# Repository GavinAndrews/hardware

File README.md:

# Nivag Swerdna's Shared Hardware Projects
This repository contains designs that have been publically shared and may be reproduced under GPL v2. i.e. That any derived versions should include full schematics and acknowledgement of the original work, and themselves be subject to the same licencing.

_"Share & Enjoy"_ 
## ROMulan PET RAMulator (with EAzy NOPulation) Version 4.1

A ROM and RAM replacement board for 6502 based microprocessors, particularly Commodore PETs and their variants.
Features include:
* 32MB RAM replacement $0000-$7FFF
* ROM replacement $9000-$FFFF selectable
* 16 individual ROM Sets stored in 4Mb Flash
* NOP Generation (causes $EA NOP to be presented to CPU on all reads)
* Power LED
* Onboard Reset switch
 
 For historic reasons this board is refered to as memory and found in the memory\ subdirectory
     
## OMNI ROMulator

A 6540 ROM replacement board for 6502 based microprocessors, particularly original Commodore PETs and their variants.
Features include:
* 32MB ROM containing 16 x 2KB Pages
* Either 2KB or 4KB ROM Replacement
* Machined Edge pins for a original chip look and feel
* Selections made using resolderable jumpers
 
 For historic reasons this board is refered to as 6540replacement and found in the 6540replacement\ subdirectory

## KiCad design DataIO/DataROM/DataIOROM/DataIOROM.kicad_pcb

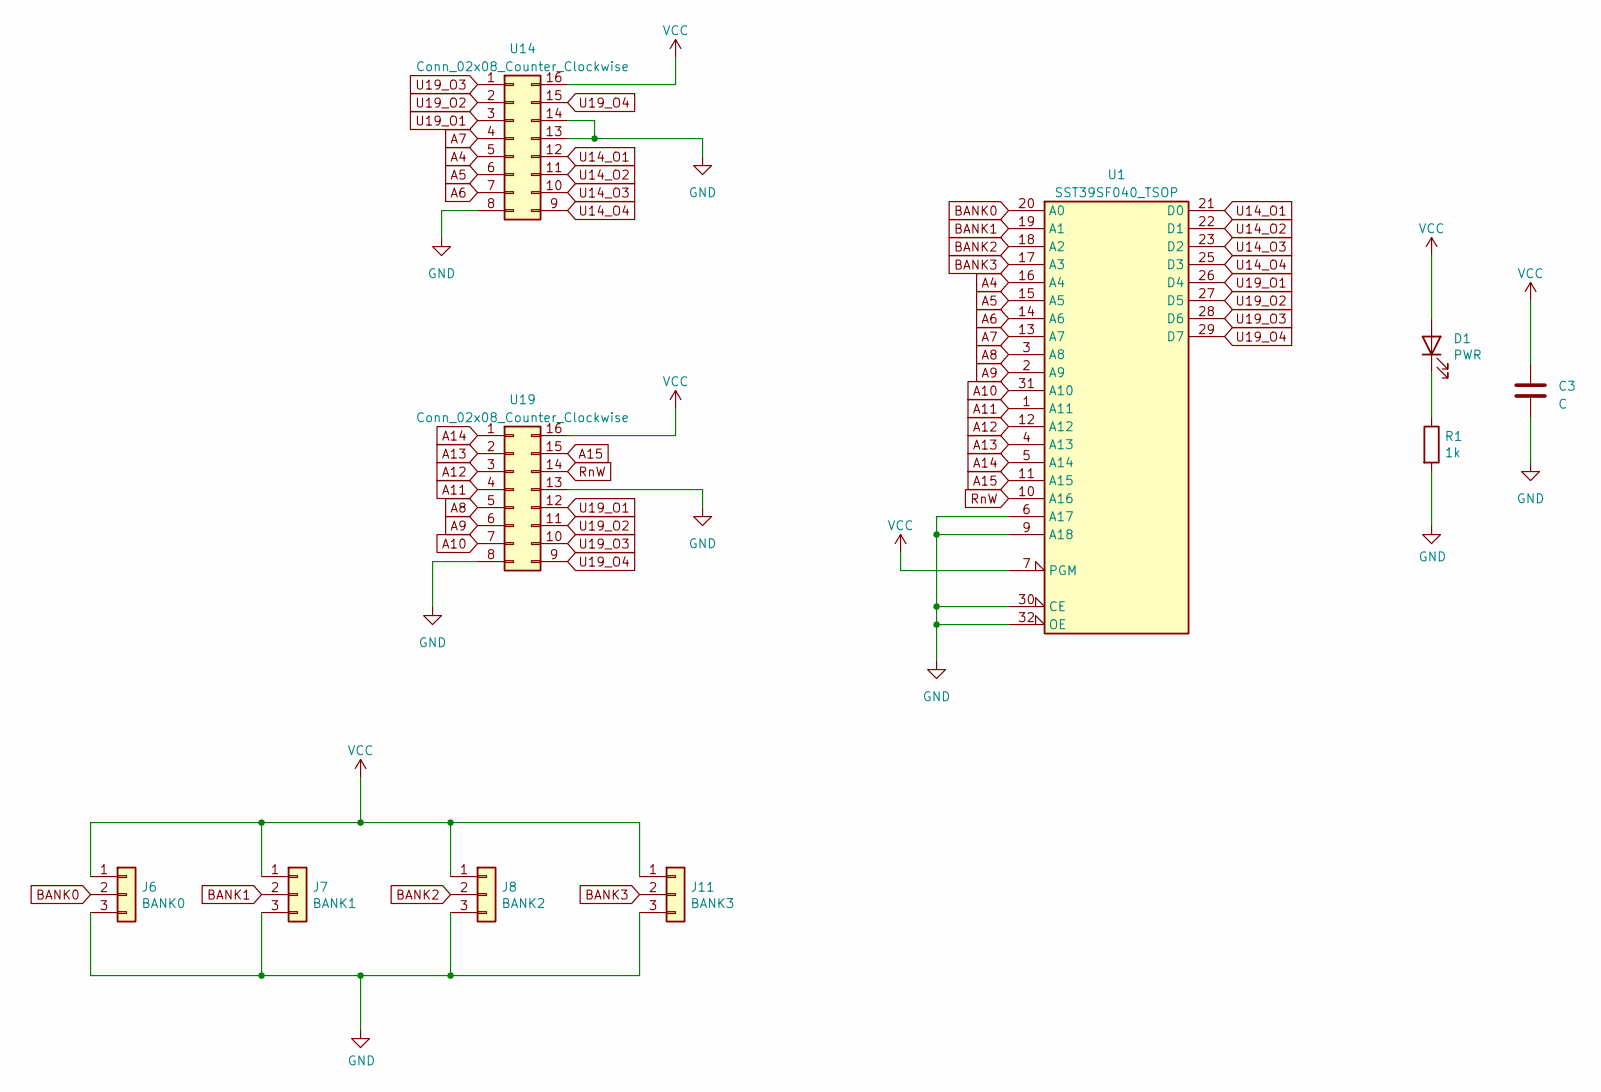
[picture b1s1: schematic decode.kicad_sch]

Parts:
C3: C; C_0603_1608Metric
D1: PWR; LED_0603_1608Metric
J6: BANK0; JP2_Arrow
J7: BANK1; JP2_Arrow
J8: BANK2; JP2_Arrow
J11: BANK3; JP2_Arrow
R1: 1k; R_0603_1608Metric
U1: SST39SF040_TSOP; TSOP-I-32_14mmx8mm_P0.5mm
U14, U19: Conn_02x08_Counter_Clockwise; DIP-16_W7.62mm

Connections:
A4: U1.16 (A4), U14.5; also elsewhere on the board
A5: U1.15 (A5), U14.6; also elsewhere on the board
A6: U1.14 (A6), U14.7; also elsewhere on the board
A7: U1.13 (A7), U14.4; also elsewhere on the board
A8: U1.3 (A8), U19.5; also elsewhere on the board
A9: U1.2 (A9), U19.6; also elsewhere on the board
A10: U1.31 (A10), U19.7; also elsewhere on the board
A11: U1.1 (A11), U19.4; also elsewhere on the board
A12: U1.12 (A12), U19.3; also elsewhere on the board
A13: U1.4 (A13), U19.2; also elsewhere on the board
A14: U1.5 (A14), U19.1
A15: U1.11 (A15), U19.15
BANK0: J6.2, U1.20 (A0)
BANK1: J7.2, U1.19 (A1)
BANK2: J8.2, U1.18 (A2)
BANK3: J11.2, U1.17 (A3)
GND: C3.2, J6.3, J7.3, J8.3, J11.3, R1.2, U1.6 (A17), U1.9 (A18), U1.24 (GND), U1.30 (CE), U1.32 (OE), U14.8, U14.13, U14.14, U19.8, U19.13; also elsewhere on the board
unnamed: D1.1 (K), R1.1
RnW: U1.10 (A16), U19.14
U14_O1: U1.21 (D0), U14.12
U14_O2: U1.22 (D1), U14.11
U14_O3: U1.23 (D2), U14.10
U14_O4: U1.25 (D3), U14.9
U19_O1: U1.26 (D4), U14.3, U19.12
U19_O2: U1.27 (D5), U14.2, U19.11
U19_O3: U1.28 (D6), U14.1, U19.10
U19_O4: U1.29 (D7), U14.15, U19.9
VCC: C3.1, D1.2 (A), J6.1, J7.1, J8.1, J11.1, U1.7 (PGM), U1.8 (VCC), U14.16, U19.16; also elsewhere on the board

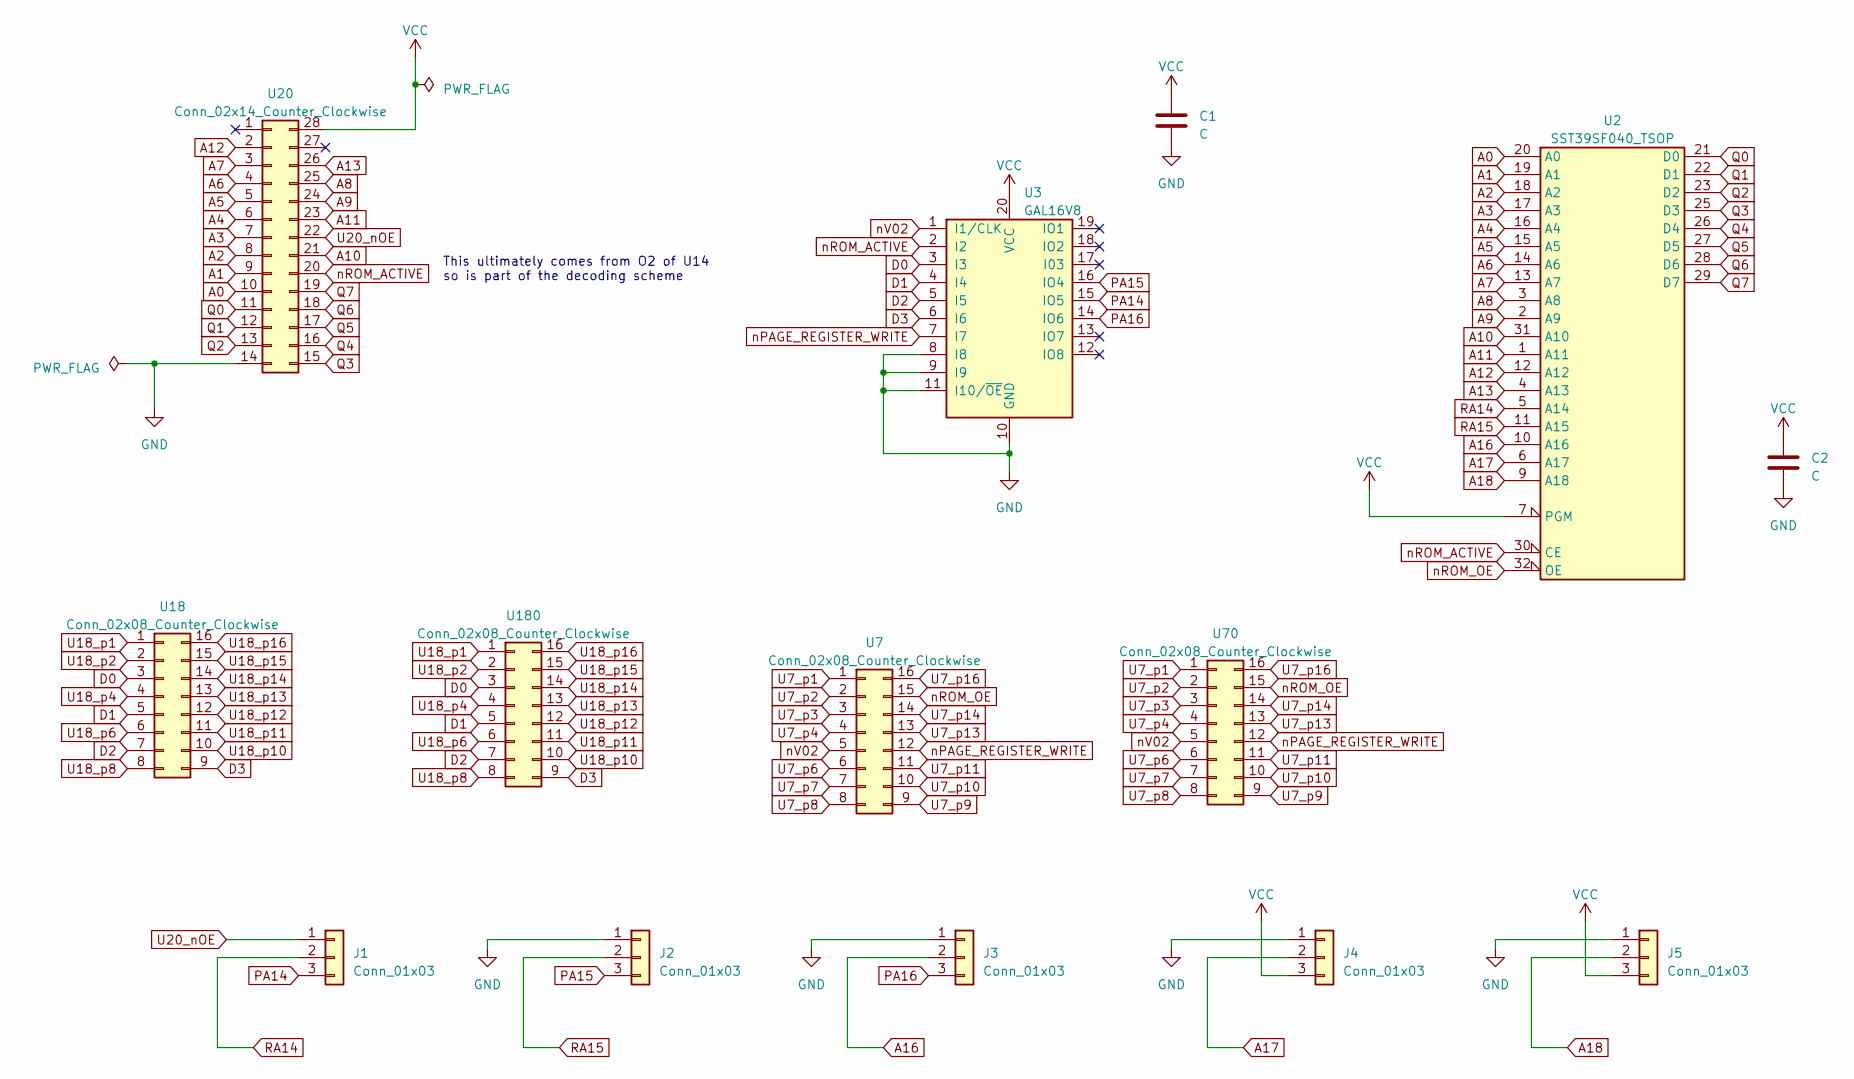
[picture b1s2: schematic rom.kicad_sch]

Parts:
C1, C2: C; C_0603_1608Metric
J1, J2, J3, J4, J5: Conn_01x03; JP2_Arrow
U2: SST39SF040_TSOP; TSOP-I-32_14mmx8mm_P0.5mm
U3: GAL16V8; DIP-20_W7.62mm_Socket
U7, U18: Conn_02x08_Counter_Clockwise; DIP-16_Frame_Bottom
U20: Conn_02x14_Counter_Clockwise; DIP-28_W15.24mm
U70, U180: Conn_02x08_Counter_Clockwise; DIP-16_Frame

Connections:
A0: U2.20 (A0), U20.10
A1: U2.19 (A1), U20.9
A2: U2.18 (A2), U20.8
A3: U2.17 (A3), U20.7
A4: U2.16 (A4), U20.6; also elsewhere on the board
A5: U2.15 (A5), U20.5; also elsewhere on the board
A6: U2.14 (A6), U20.4; also elsewhere on the board
A7: U2.13 (A7), U20.3; also elsewhere on the board
A8: U2.3 (A8), U20.25; also elsewhere on the board
A9: U2.2 (A9), U20.24; also elsewhere on the board
A10: U2.31 (A10), U20.21; also elsewhere on the board
A11: U2.1 (A11), U20.23; also elsewhere on the board
A12: U2.12 (A12), U20.2; also elsewhere on the board
A13: U2.4 (A13), U20.26; also elsewhere on the board
A16: J3.2, U2.10 (A16)
A17: J4.2, U2.6 (A17)
A18: J5.2, U2.9 (A18)
D0: U3.3 (I3), U18.3, U180.3
D1: U3.4 (I4), U18.5, U180.5
D2: U3.5 (I5), U18.7, U180.7
D3: U3.6 (I6), U18.9, U180.9
GND: C1.2, C2.2, J2.1, J3.1, J4.1, J5.1, U2.24 (GND), U3.8 (I8), U3.9 (I9), U3.10 (GND), U3.11 (I10/~OE), U20.14; also elsewhere on the board
PA14: J1.3, U3.15 (IO5)
PA15: J2.3, U3.16 (IO4)
PA16: J3.3, U3.14 (IO6)
Q0: U2.21 (D0), U20.11
Q1: U2.22 (D1), U20.12
Q2: U2.23 (D2), U20.13
Q3: U2.25 (D3), U20.15
Q4: U2.26 (D4), U20.16
Q5: U2.27 (D5), U20.17
Q6: U2.28 (D6), U20.18
Q7: U2.29 (D7), U20.19
RA14: J1.2, U2.5 (A14)
RA15: J2.2, U2.11 (A15)
U7_p1: U7.1, U70.1
U7_p2: U7.2, U70.2
U7_p3: U7.3, U70.3
U7_p4: U7.4, U70.4
U7_p6: U7.6, U70.6
U7_p7: U7.7, U70.7
U7_p8: U7.8, U70.8
U7_p9: U7.9, U70.9
U7_p10: U7.10, U70.10
U7_p11: U7.11, U70.11
U7_p13: U7.13, U70.13
U7_p14: U7.14, U70.14
U7_p16: U7.16, U70.16
U18_p1: U18.1, U180.1
U18_p2: U18.2, U180.2
U18_p4: U18.4, U180.4
U18_p6: U18.6, U180.6
U18_p8: U18.8, U180.8
U18_p10: U18.10, U180.10
U18_p11: U18.11, U180.11
U18_p12: U18.12, U180.12
U18_p13: U18.13, U180.13
U18_p14: U18.14, U180.14
U18_p15: U18.15, U180.15
U18_p16: U18.16, U180.16
U20_nOE: J1.1, U20.22
VCC: C1.1, C2.1, J4.3, J5.3, U2.7 (PGM), U2.8 (VCC), U3.20 (VCC), U20.28; also elsewhere on the board
nPAGE_REGISTER_WRITE: U3.7 (I7), U7.12, U70.12
nROM_ACTIVE: U2.30 (CE), U3.2 (I2), U20.20
nROM_OE: U2.32 (OE), U7.15, U70.15
nV02: U3.1 (I1/CLK), U7.5, U70.5

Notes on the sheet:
This ultimately comes from O2 of U14 so is part of the decoding scheme

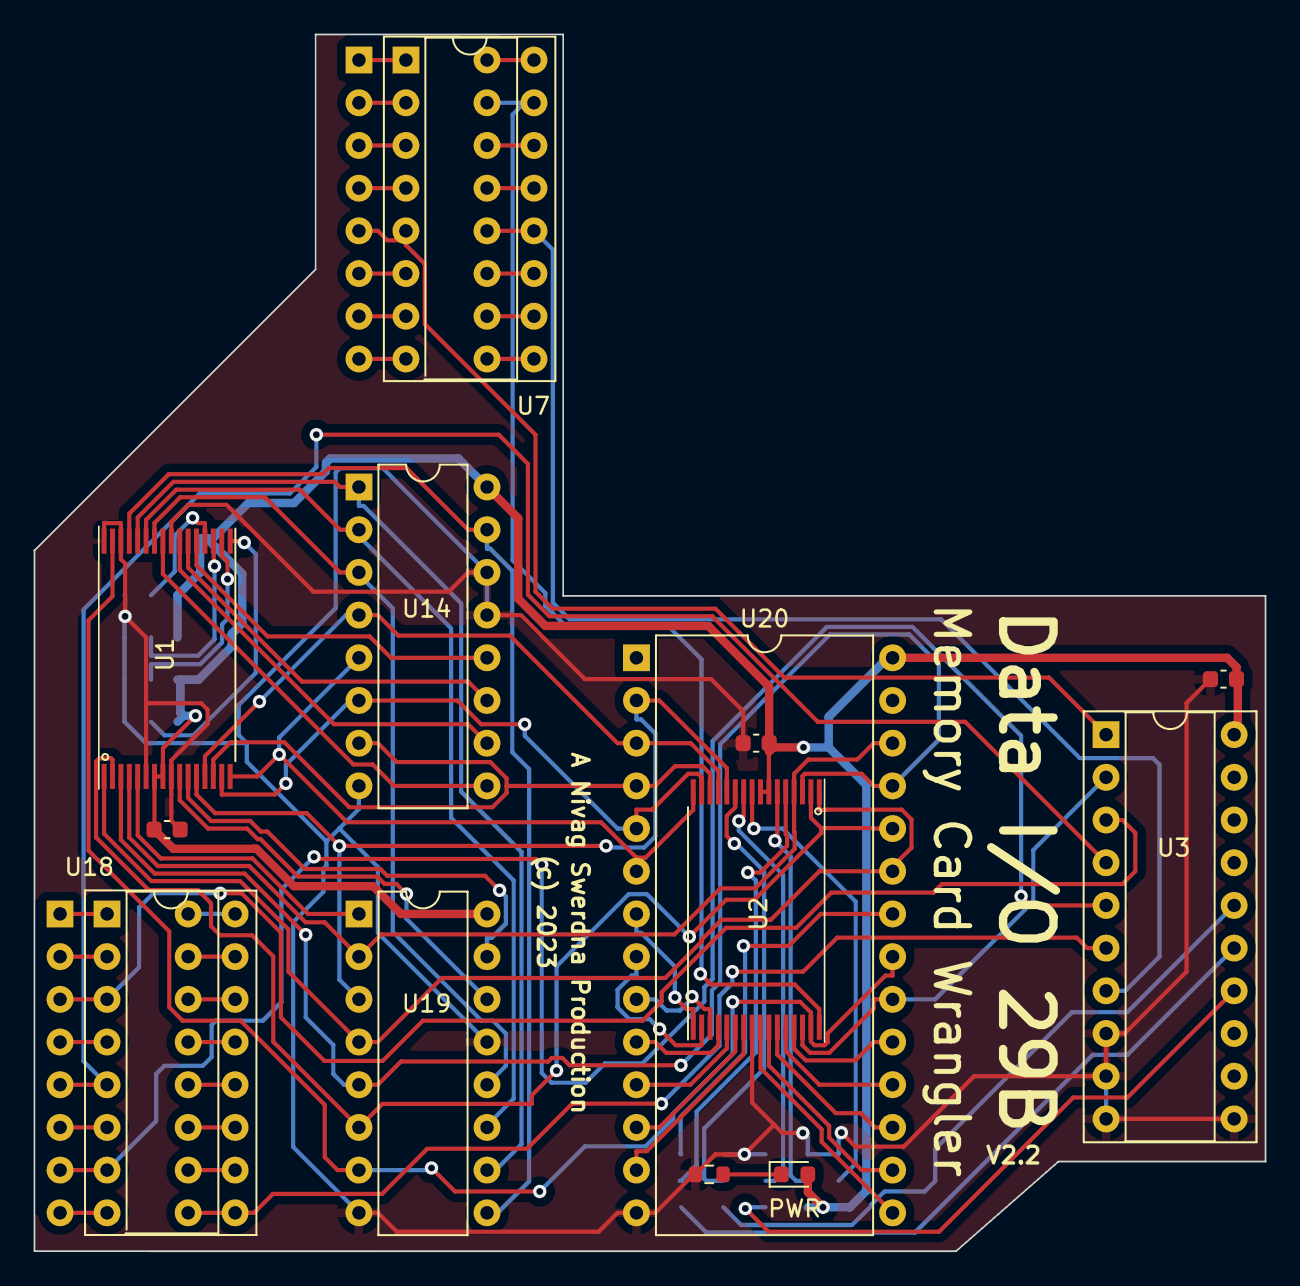
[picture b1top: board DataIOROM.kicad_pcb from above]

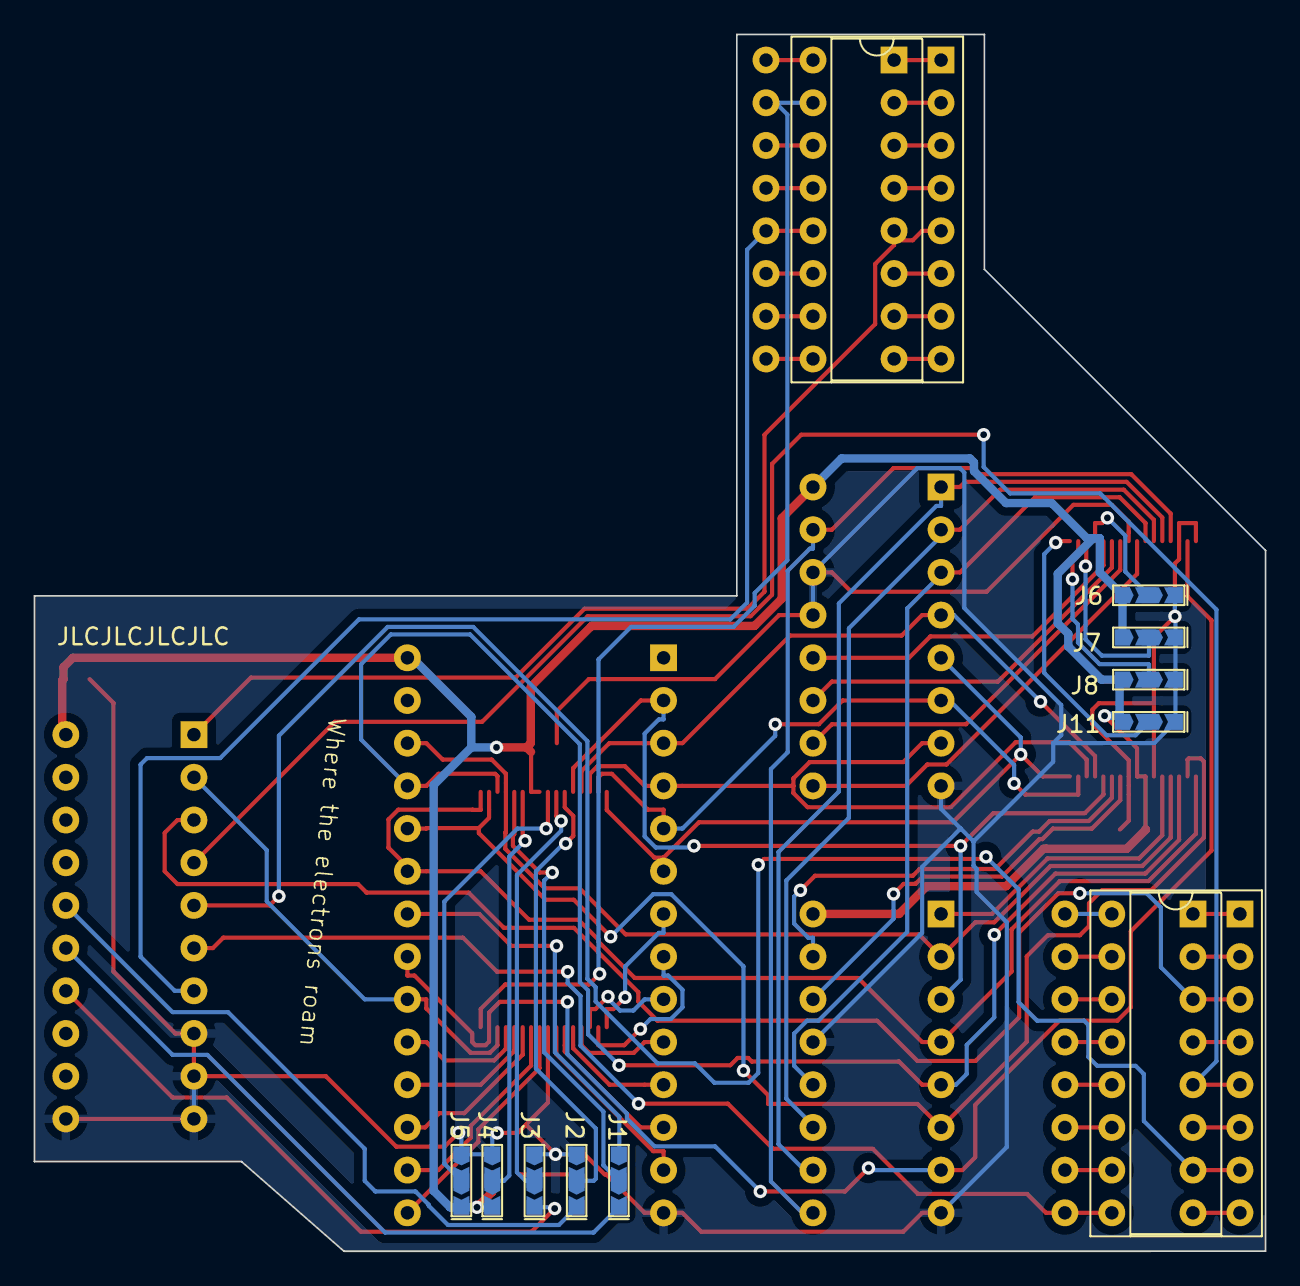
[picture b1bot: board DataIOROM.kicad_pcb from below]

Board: 2 copper layers, 73.2 x 72.4 mm, 24 parts (9 on the bottom side), 82 nets.

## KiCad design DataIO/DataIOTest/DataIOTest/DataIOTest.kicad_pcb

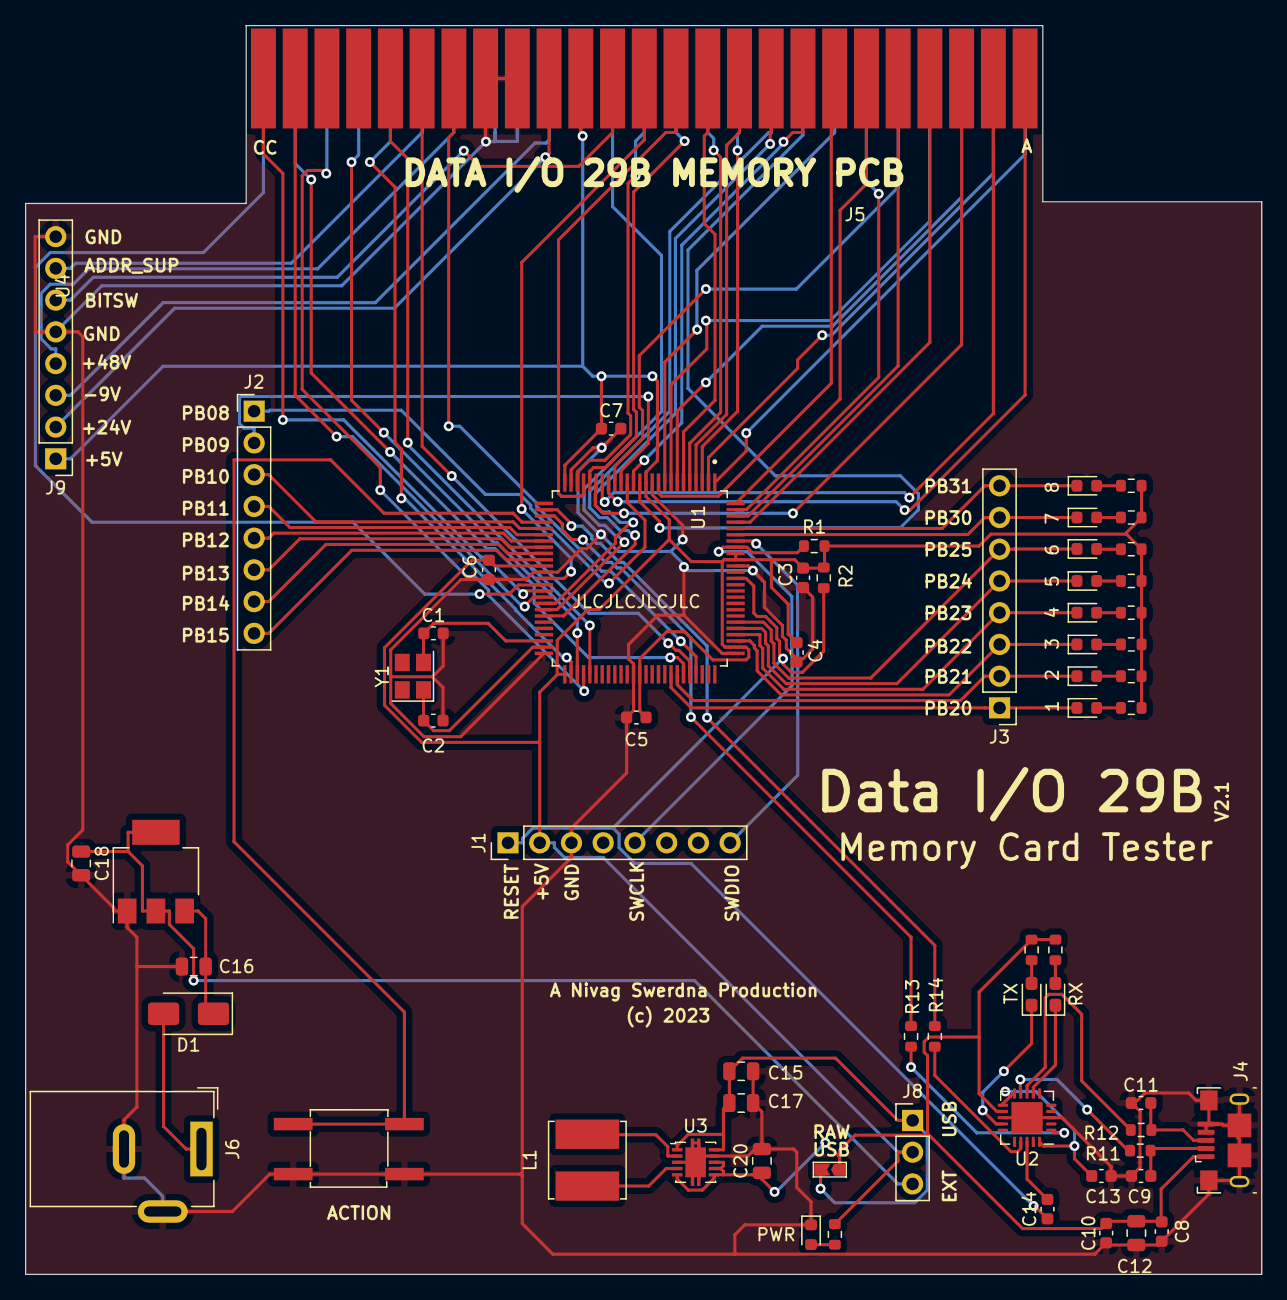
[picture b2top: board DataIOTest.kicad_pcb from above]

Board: 2 copper layers, 98.9 x 99.9 mm, 64 parts (0 on the bottom side), 96 nets.

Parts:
C1, C2: 8p; C_0603_1608Metric
C3, C4, C5, C7: .1u; C_0603_1608Metric
C6: 1u; C_0603_1608Metric
C8: 10n; C_0603_1608Metric
C9, C11: 47p; C_0603_1608Metric
C10, C13, C14: 100n; C_0603_1608Metric
C12: 10u; C_0805_2012Metric
C15, C17, C18, C20: 22u; C_0805_2012Metric
C16: 10u 16V; C_0805_2012Metric
D1: M7; D_SMA
J1, J2, J3, J9: Conn_01x08; PinHeader_1x08_P2.54mm_Vertical
J4: USB_B_Micro; USB_Micro-B_10118193
J5: MEMORY CARD; DATAIO_MEMORY_CONNECTOR
J6: Barrel_Jack_Switch; DC10A
J7: USB_RAW; JP1_Arrow
J8: PWR_SELECT; PinHeader_1x03_P2.54mm_Vertical
L1: 4.7u; L_Bourns_SRN6045TA
LED1: 1; LED_0603_1608Metric
LED2: 2; LED_0603_1608Metric
LED3: 3; LED_0603_1608Metric
LED4: 4; LED_0603_1608Metric
LED5: 5; LED_0603_1608Metric
LED6: 6; LED_0603_1608Metric
LED7: 7; LED_0603_1608Metric
LED8: 8; LED_0603_1608Metric
LED9: TX; LED_0603_1608Metric_Pad1.05x0.95mm_HandSolder
LED10: RX; LED_0603_1608Metric_Pad1.05x0.95mm_HandSolder
LED11: PWR; LED_0603_1608Metric
R1, R2, R3, R4, R5, R6, R7, R8, R9, R10: 10k; R_0603_1608Metric
R11, R12: 27; R_0603_1608Metric
R13, R14, R15, R16, R17: 1k; R_0603_1608Metric
SW1: Tactile_Switch; TACTILE_SW
U1: ATSAMC21N18A-ANT; QFP50P1600X1600X120-100N
U2: FT231XQ; QFN-20-1EP_4x4mm_P0.5mm_EP2.5x2.5mm
U3: TPS63002DRCT; VSON-10-1EP_3x3mm_P0.5mm_EP1.65x2.4mm
U4: AP1117-50; SOT-223-3_TabPin2
Y1: 16MHz; Crystal_SMD_3225-4Pin_3.2x2.5mm

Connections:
+5V: C3.1, C4.1, C5.1, C6.1, C7.1, J1.2, J5.15 (+5V), J5.S (+5V), J8.2, J9.1, R1.1, R2.1, R3.2, R4.2, R5.2, R6.2, R7.2, R8.2, R9.2, R10.2, R17.2, U1.12 (VDDANA), U1.25 (VDDIO), U1.36 (VDDIO), U1.51 (VDDIO), U1.63 (VDDIO), U1.77 (VDDIO), U1.91 (VDDCORE), U1.92 (VDDIN)
+24V: J5.T (+24V), J9.2
+48V: J5.19 (+48V), J9.4
-9V: J5.16 (-9V), J9.3
A0: J5.1 (A0), U1.1 (PA00)
A1: J5.2 (A1), U1.2 (PA01)
A2: J5.3 (A2), U1.7 (PA02)
A3: J5.4 (A3), U1.8 (PA03)
A4: J5.5 (A4), U1.17 (PA04)
A5: J5.A (A5), U1.18 (PA05)
A6: J5.B (A6), U1.19 (PA06)
A7: J5.C (A7), U1.20 (PA07)
A8: J5.D (A8), U1.97 (PB00)
A9: J5.E (A9), U1.98 (PB01)
A10: J5.6 (A10), U1.99 (PB02)
A11: J5.F (A11), U1.100 (PB03)
A12: J5.7 (A12), U1.9 (PB04)
A13: J5.H (A13), U1.10 (PB05)
A14: J5.8 (A14), U1.13 (PB06)
A15: J5.J (A15), U1.14 (PB07)
ADDR_SUP: J5.20 (ADDR_SUP), J9.7
BITSW: J5.R (BITSW), J9.6
C1: J5.21 (C1), U1.52 (PA16)
C2: J5.22 (C2), U1.53 (PA17)
DO1: J5.10 (DO1), U1.3 (PC00)
DO2: J5.L (DO2), U1.4 (PC01)
DO3: J5.11 (DO3), U1.5 (PC02)
DO4: J5.M (DO4), U1.6 (PC03)
DO5: J5.12 (DO5), U1.21 (PC05)
DO6: J5.N (DO6), U1.22 (PC06)
DO7: J5.13 (DO7), U1.23 (PC07)
DO8: J5.P (DO8), U1.38 (PC08)
EXT_5V: C18.1, J8.3, U4.2 (VO)
GATE_ENABLE: J5.W (GATE_ENABLE), U1.72 (PA22)
GND: C1.2, C2.2, C3.2, C4.2, C5.2, C6.2, C7.2, C8.1, C9.1, C10.1, C11.1, C12.1, C13.1, C15.2, C16.2, C17.2, C18.2, C20.2, J1.3, J4.4 (ID), J4.5 (GND), J4.6 (Shield), J5.17 (GND), J5.18 (GND), J5.U (GND), J5.V (GND), J6.2, J6.3, J9.5, J9.8, LED11.1 (K), SW1.3, SW1.4, U1.11 (GND), U1.24 (GND), U1.37 (GND), U1.50 (GND), U1.62 (GND), U1.76 (GND), U1.90 (GND), U2.3 (GND), U2.13 (GND), U2.21 (GND), U3.3 (PGND), U3.9 (GND), U3.11 (PAD), U4.1 (GND)
LED1: J3.1, LED1.1 (K), U1.68 (PB20)
LED2: J3.2, LED2.1 (K), U1.69 (PB21)
LED3: J3.3, LED3.1 (K), U1.78 (PB22)
LED4: J3.4, LED4.1 (K), U1.79 (PB23)
LED5: J3.5, LED5.1 (K), U1.80 (PB24)
LED6: J3.6, LED6.1 (K), U1.81 (PB25)
LED7: J3.7, LED7.1 (K), U1.95 (PB30)
LED8: J3.8, LED8.1 (K), U1.96 (PB31)
MCU_RESET: C14.1, J1.1, R2.2, U1.88 (~RESET)
unnamed: D1.2 (A), J6.1
unnamed: C16.1, D1.1 (K), U4.3 (VI)
unnamed: J2.1, U1.15 (PB08)
unnamed: J2.2, U1.16 (PB09)
unnamed: J2.3, U1.30 (PB10)
unnamed: J2.4, U1.31 (PB11)
unnamed: J2.5, U1.32 (PB12)
unnamed: J2.6, U1.33 (PB13)
unnamed: J2.7, U1.34 (PB14)
unnamed: J2.8, U1.35 (PB15)
unnamed: C11.2, J4.3 (D+), R12.2
unnamed: C9.2, J4.2 (D-), R11.2
unnamed: LED1.2 (A), R3.1
unnamed: LED2.2 (A), R5.1
unnamed: LED3.2 (A), R7.1
unnamed: LED4.2 (A), R9.1
unnamed: LED5.2 (A), R4.1
unnamed: LED6.2 (A), R6.1
unnamed: LED7.2 (A), R8.1
unnamed: LED8.2 (A), R10.1
unnamed: LED9.2 (A), R15.1
unnamed: LED9.1 (K), U2.14 (CBUS1)
unnamed: LED10.2 (A), R16.1
unnamed: LED10.1 (K), U2.7 (CBUS2)
unnamed: LED11.2 (A), R17.1
unnamed: C13.2, U2.10 (3V3OUT), U2.11 (~RESET), U2.20 (VCCIO)
unnamed: R14.2, U2.1 (RXD)
unnamed: R13.1, U2.17 (TXD)
unnamed: R11.1, U2.9 (USBDM)
unnamed: R12.1, U2.8 (USBDP)
unnamed: C14.2, U2.18 (~DTR)
unnamed: L1.1, U3.4 (L1)
unnamed: L1.2, U3.2 (L2)
OVER_C: J5.K (OVER_C), U1.42 (PC12)
P1nP0: J5.BB (P1nP0), U1.41 (PC11)
RX: R13.2, U1.27 (PA09)
RnW: J5.CC (RnW), U1.40 (PC10)
SW1: SW1.1, SW1.2, U1.29 (PA11)
SWCLK: J1.5, R1.2, U1.93 (PA30)
SWDIO: J1.8, U1.94 (PA31)
TX: R14.1, U1.28 (PA10)
USB_5V: C15.1, C17.1, J7.2, J8.1, U3.1 (VOUT), U3.10 (FB)
USB_PWR: C8.2, C10.2, C12.2, C20.1, J4.1 (VBUS), J7.1, R15.2, R16.2, U2.12 (VCC), U3.5 (VIN), U3.6 (EN), U3.7 (PS_SYNC), U3.8 (VINA)
XIN: C1.1, U1.48 (PA14), Y1.2
XOUT: C2.1, U1.49 (PA15), Y1.1
nC3: J5.23 (nC3), U1.54 (PA18)
nC4: J5.Y (nC4), U1.55 (PA19)
nC7: J5.24 (nC7), U1.70 (PA20)
nC11: J5.X (nC11), U1.71 (PA21)
nPULSE: J5.9 (nPULSE), U1.44 (PC14)
nV02: J5.25 (nV02), U1.39 (PC09)
nVPULSE: J5.14 (nVPULSE), U1.43 (PC13)

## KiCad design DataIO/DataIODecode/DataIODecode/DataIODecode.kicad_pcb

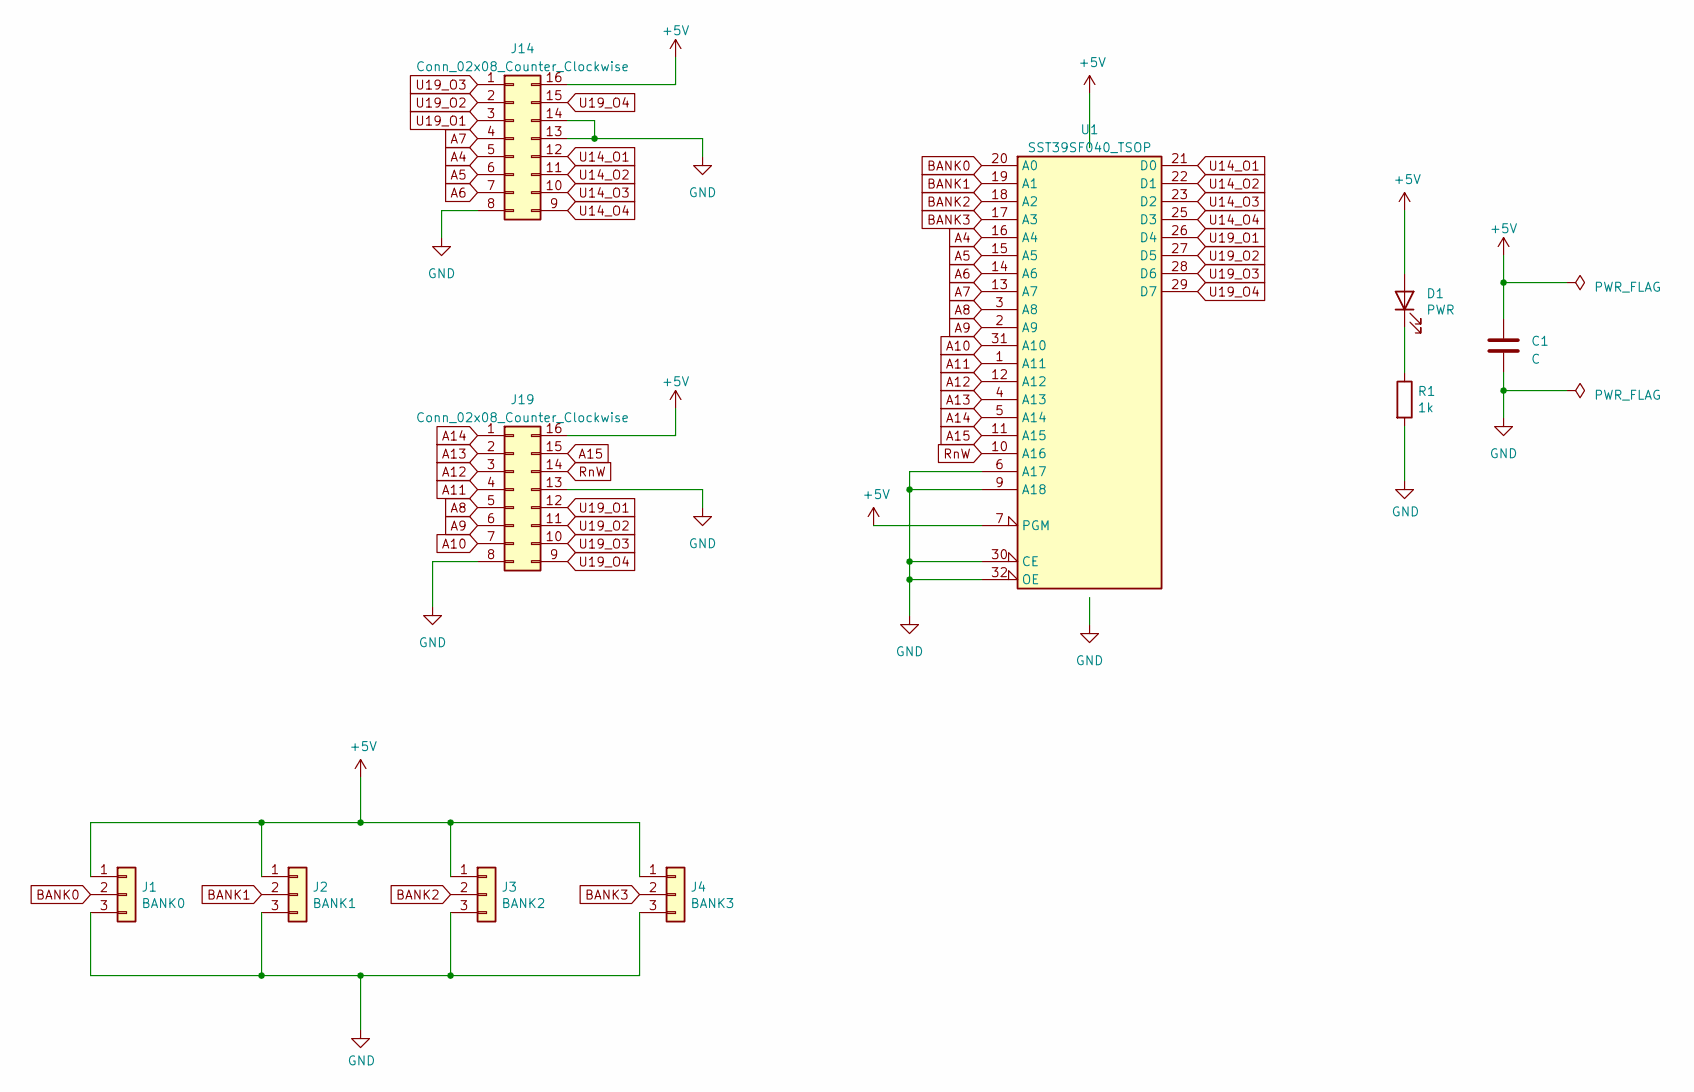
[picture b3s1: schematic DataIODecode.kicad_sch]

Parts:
C1: C; C_0603_1608Metric
D1: PWR; LED_0603_1608Metric
J1: BANK0; JP2_Arrow
J2: BANK1; JP2_Arrow
J3: BANK2; JP2_Arrow
J4: BANK3; JP2_Arrow
J14, J19: Conn_02x08_Counter_Clockwise; DIP-16_W7.62mm
R1: 1k; R_0603_1608Metric
U1: SST39SF040_TSOP; TSOP-I-32_14mmx8mm_P0.5mm

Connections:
+5V: C1.1, D1.2 (A), J1.1, J2.1, J3.1, J4.1, J14.16, J19.16, U1.7 (PGM), U1.8 (VCC)
A4: J14.5, U1.16 (A4)
A5: J14.6, U1.15 (A5)
A6: J14.7, U1.14 (A6)
A7: J14.4, U1.13 (A7)
A8: J19.5, U1.3 (A8)
A9: J19.6, U1.2 (A9)
A10: J19.7, U1.31 (A10)
A11: J19.4, U1.1 (A11)
A12: J19.3, U1.12 (A12)
A13: J19.2, U1.4 (A13)
A14: J19.1, U1.5 (A14)
A15: J19.15, U1.11 (A15)
BANK0: J1.2, U1.20 (A0)
BANK1: J2.2, U1.19 (A1)
BANK2: J3.2, U1.18 (A2)
BANK3: J4.2, U1.17 (A3)
GND: C1.2, J1.3, J2.3, J3.3, J4.3, J14.8, J14.13, J14.14, J19.8, J19.13, R1.2, U1.6 (A17), U1.9 (A18), U1.24 (GND), U1.30 (CE), U1.32 (OE)
unnamed: D1.1 (K), R1.1
RnW: J19.14, U1.10 (A16)
U14_O1: J14.12, U1.21 (D0)
U14_O2: J14.11, U1.22 (D1)
U14_O3: J14.10, U1.23 (D2)
U14_O4: J14.9, U1.25 (D3)
U19_O1: J14.3, J19.12, U1.26 (D4)
U19_O2: J14.2, J19.11, U1.27 (D5)
U19_O3: J14.1, J19.10, U1.28 (D6)
U19_O4: J14.15, J19.9, U1.29 (D7)

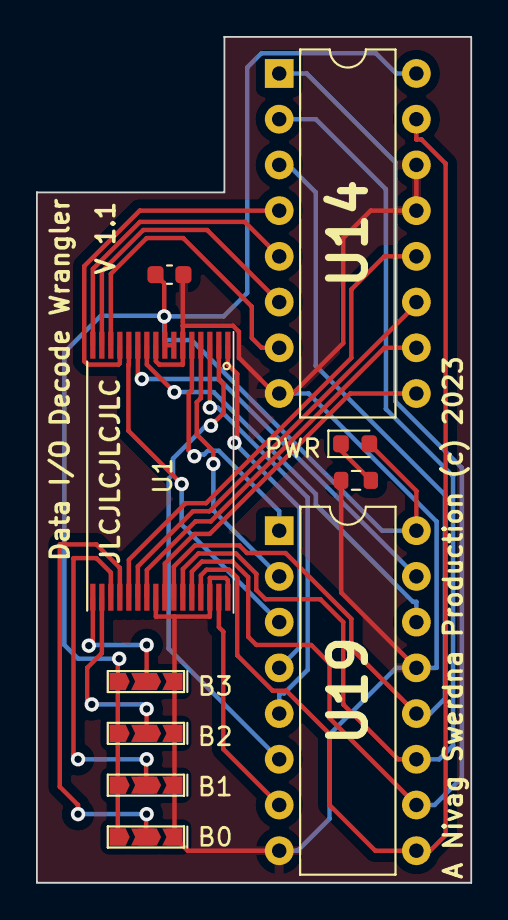
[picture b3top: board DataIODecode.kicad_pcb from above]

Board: 2 copper layers, 24.1 x 47.0 mm, 10 parts (0 on the bottom side), 28 nets.

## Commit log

2020-12-30 Added memory
2020-12-30 Added image of PCB
2021-01-01 Additional helpful info on the testers
2021-01-06 Added OMNI Image
2021-01-06 Fix url
2021-01-06 Fixing images
2021-01-06 Added memory image
2021-01-06 Added a bit of documentation
2021-01-06 Added the Multi1 images
2021-01-06 PCB Images
2021-01-10 added ROM Sets
2021-01-16 ROMulan OMNI New Owner doc
2021-02-05 More doc
2021-02-20 Update to account for new chip and slide mechanism
2021-02-20 Chip And Slide
2021-04-20 Added TSOP Flash Contents
2021-06-23 VideoRAM doc
2022-08-14 New Owner 23xx
2022-08-14 Move into correct folder
2025-08-31 Catchup to August 2025
2025-08-31 Added manual
2026-01-02 Generated v2.2 Gerbers
2026-01-02 Tidy up v2.2 files
2026-05-26 HDL for Data I/O Expanded
2026-05-26 Tidy

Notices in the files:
DataIO/DataIODecode/DataIODecode/DataIODecode.kicad_pcb:
A Nivag Swerdna Production (c) 2023
DataIO/DataIOTest/DataIOTest/DataIOTest.kicad_pcb:
(c) 2023
